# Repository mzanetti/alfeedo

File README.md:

# Alfeedo

A fully featured, smart home integrated cat feeder. 

This repository contains the firmware for the 3D printed cat feeder Alfeedo.

## Features

* Controls a TMC2209 stepper motor to dispense food (including jam detection and recovery)
* Supports operation and setup using a 128x32 display and Buttons
* Built-in web interface
* REST API

| Main view | Timer settings | Logs | Settings |
| :--- | :--- | :--- | :--- |
|  |  |  |  |

## How to build

3D print model files along with a bill of materials are available on Makerworld. 

[Makerworld - Alfeedo](https://makerworld.com/en/models/2506745-alfeedo-smart-cat-feeder)

Follow print and assembly instructions provided with the model files.

Electronics wiring can be simplified by ordering the Alfeedo PCB using the provided Gerber files in [pcb/](https://github.com/mzanetti/alfeedo/tree/main/pcb).

-Flash the device using the [web flasher](https://mzanetti.github.io/alfeedo/main/flasher/).

-Connect with the Alfeedo-WIFI-AP

-Navigate to alfeedo.local and set network credentials.

Note that the provided firmware assumes wiring to look like on the Alfeedo PCB. If instead you prefer using a different setup, you'll have to build the firmware yourself and adjust the pins in hwsettings.h.

## Building

This project is based on [platformio](https://platformio.org/).

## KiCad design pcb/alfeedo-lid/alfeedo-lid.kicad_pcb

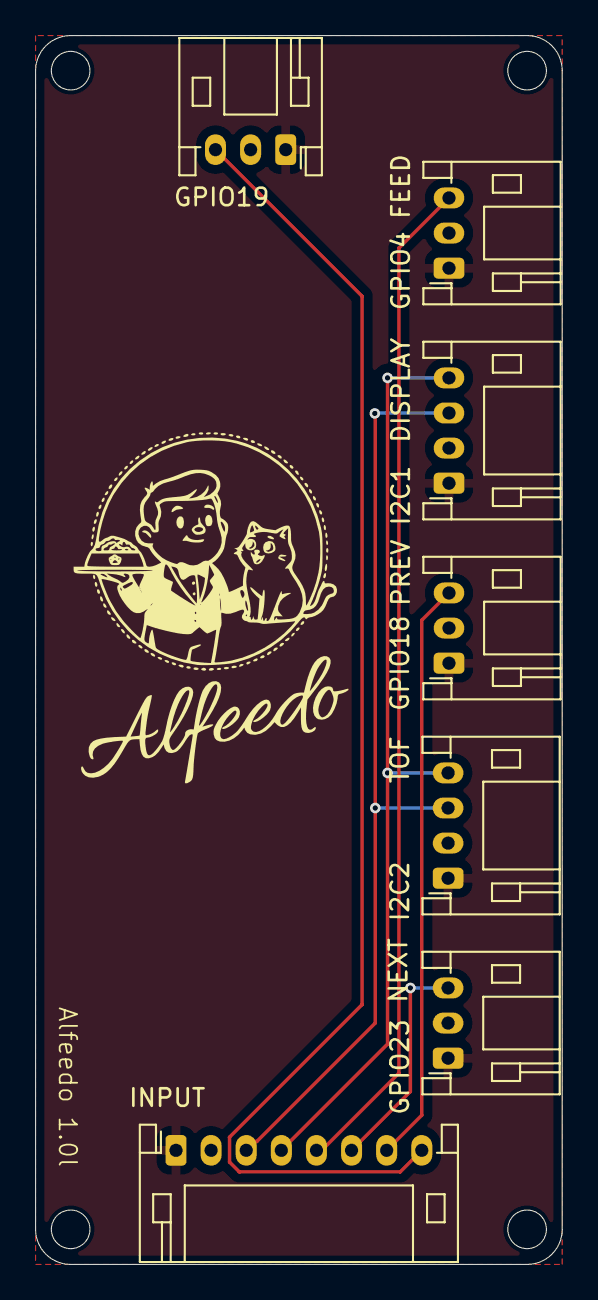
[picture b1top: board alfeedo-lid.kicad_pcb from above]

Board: 2 copper layers, 30.0 x 70.0 mm, 11 parts (0 on the bottom side), 8 nets.

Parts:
GPIO4: FEED; JST_PH_S3B-PH-K_1x03_P2.00mm_Horizontal
GPIO18: PREV; JST_PH_S3B-PH-K_1x03_P2.00mm_Horizontal
GPIO19: RESERVED; JST_PH_S3B-PH-K_1x03_P2.00mm_Horizontal
GPIO23: NEXT; JST_PH_S3B-PH-K_1x03_P2.00mm_Horizontal
H1, H2, H3, H4: MountingHole; MountingHole_2.2mm_M2
I2C1: DISPLAY; JST_PH_S4B-PH-K_1x04_P2.00mm_Horizontal
I2C2: TOF; JST_PH_S4B-PH-K_1x04_P2.00mm_Horizontal
J1: INPUT; JST_PH_S8B-PH-K_1x08_P2.00mm_Horizontal

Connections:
/GND: GPIO4.2, GPIO18.2, GPIO19.2, GPIO23.2, I2C1.2, I2C2.2, J1.2
/GPIO_FEED: GPIO4.3, J1.5
/GPIO_NEXT: GPIO23.3, J1.6
/GPIO_PREV: GPIO18.3, J1.7
/GPIO_RESERVED: GPIO19.3, J1.8
/PWR: GPIO4.1, GPIO18.1, GPIO19.1, GPIO23.1, I2C1.1, I2C2.1, J1.1
/SCL: I2C1.4, I2C2.4, J1.4
/SDA: I2C1.3, I2C2.3, J1.3

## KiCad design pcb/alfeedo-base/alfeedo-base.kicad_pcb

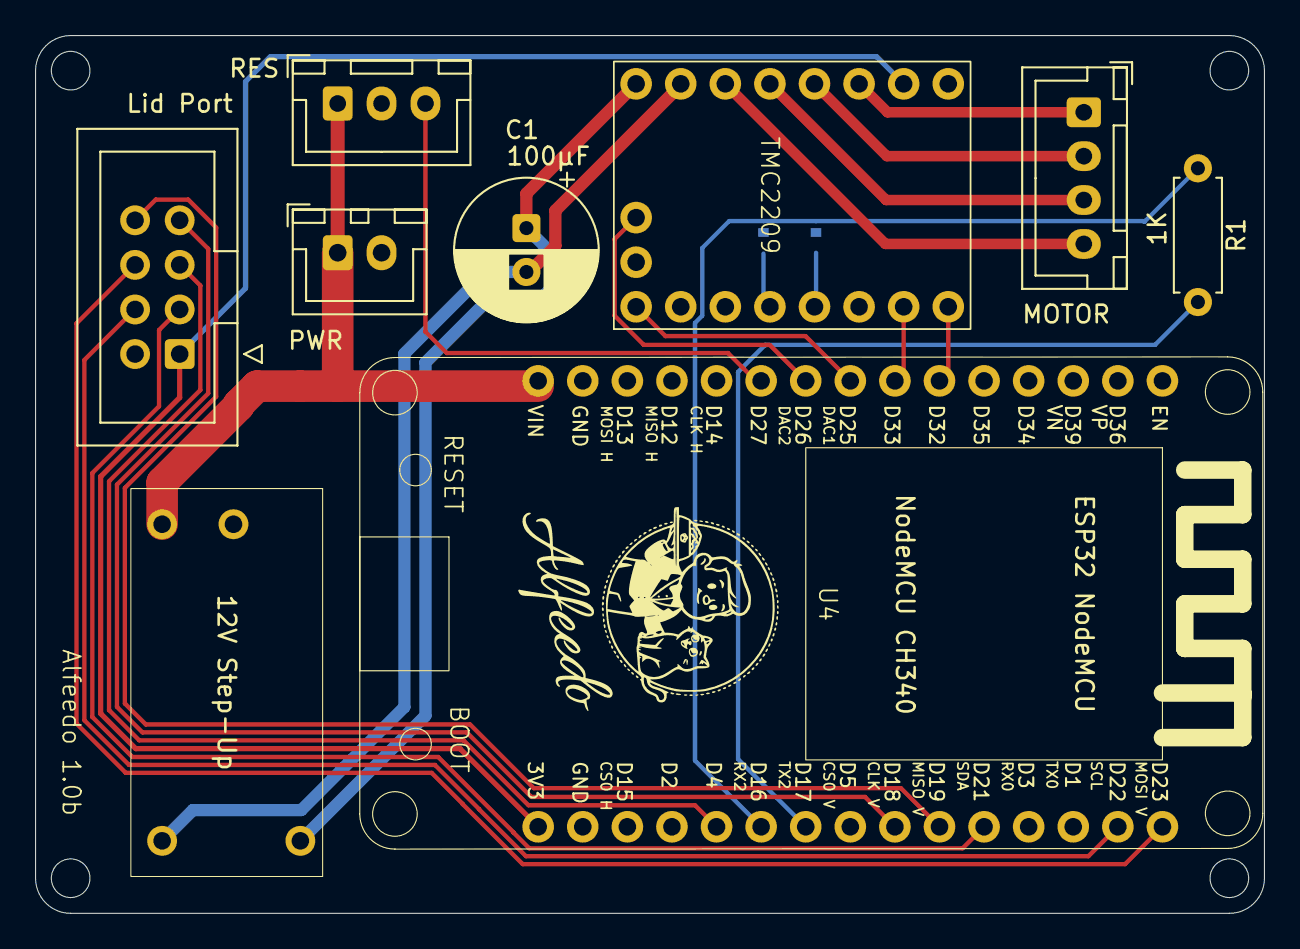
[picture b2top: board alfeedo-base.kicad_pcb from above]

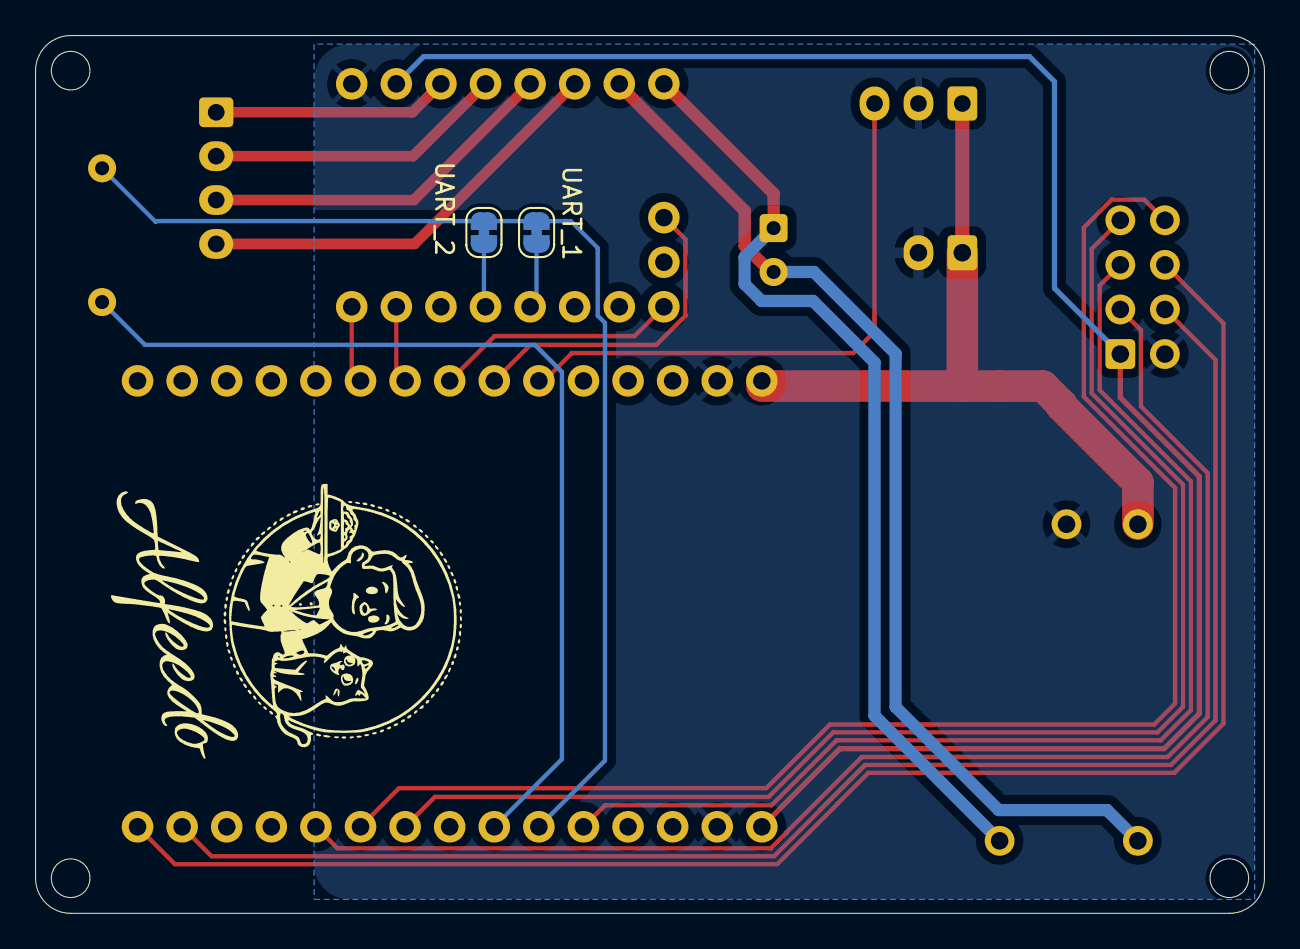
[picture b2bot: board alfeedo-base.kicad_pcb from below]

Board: 2 copper layers, 70.0 x 50.0 mm, 15 parts (2 on the bottom side), 24 nets.

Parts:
C1: 100µF; CP_Radial_D8.0mm_P2.50mm
H1, H2, H3, H4: MountingHole; MountingHole_2.2mm_M2
J1: RES; JST_XH_B3B-XH-A_1x03_P2.50mm_Vertical
J4: PWR; JST_XH_B2B-XH-A_1x02_P2.50mm_Vertical
J6: MOTOR; JST_XH_B4B-XH-A_1x04_P2.50mm_Vertical
JP1: UART_2; SolderJumper-2_P1.3mm_Bridged_RoundedPad1.0x1.5mm
JP2: UART_1; SolderJumper-2_P1.3mm_Bridged_RoundedPad1.0x1.5mm
R1: 1K; R_Axial_DIN0207_L6.3mm_D2.5mm_P7.62mm_Horizontal
TMC2209: TMC2209
U1: 12V Step-Up; 12V Step-up
U2: Lid Port; IDC-Header_2x04_P2.54mm_Vertical
U4: ESP32 NodeMCU; NodeMCU CH340

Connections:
/3.3V: TMC2209.15 (VDD), U2.1 (3.3V), U4.30 (3.3V)
/GND: J1.2, J4.2, TMC2209.16 (GND), U1.1 (-IN), U2.2 (GND), U4.14 (GND), U4.29 (GND)
/GND_M: C1.2, TMC2209.10 (GND_M), U1.3 (-OUT)
/GPIO_DIAG: TMC2209.18 (DIAG), U4.9 (D26)
/GPIO_DIR: TMC2209.8 (DIR), U4.6 (D32)
/GPIO_EN: TMC2209.1 (EN), U4.8 (D25)
/GPIO_FEED: U2.5 (BTN_FEED), U4.26 (D4)
/GPIO_NEXT: U2.6 (BTN_NEXT), U4.16 (D23/MOSI)
/GPIO_PREV: U2.7 (BTN_PREV), U4.22 (D18/CLK)
/GPIO_RES: U2.8 (RES), U4.21 (D19/MISO)
/GPIO_STEP: TMC2209.7 (STEP), U4.7 (D33)
/Motor_A1: J6.3, TMC2209.12 (A1)
/Motor_A2: J6.4, TMC2209.11 (A2)
/Motor_B1: J6.2, TMC2209.13 (B1)
/Motor_B2: J6.1, TMC2209.14 (B2)
/SCL: U2.4 (SCL), U4.17 (D22/SCL)
/SDA: U2.3 (SDA), U4.20 (D21/SDA)
/UART_RX: JP1.1 (A), JP2.1 (A), R1.2, U4.25 (D16/RX2)
/UART_TX: R1.1, U4.24 (D17/TX2)
/VIN: J1.1, J4.1, U1.2 (+IN), U4.15 (VIN)
/V_M: C1.1, TMC2209.9 (VM), U1.4 (+OUT)
unnamed: J1.3, U4.10 (D27)
unnamed: JP1.2 (B), TMC2209.5 (PDN_UART_TX)
unnamed: JP2.2 (B), TMC2209.4 (PDN_UART_RX)

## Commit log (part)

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2026-03-02 Initial import
2026-03-02 Add github action
    Add github action to build with platformio
2026-03-02 Build with newer toolchain
2026-03-02 archive artifacts
2026-03-02 deploy: 7b175032e379fcab0c805f331938c22b007cf090
2026-03-03 Add github pages publish
2026-03-03 deploy: 23218cf0d6253eb7ced624008aa3cf3002dfaa0b
2026-03-05 Add readme
2026-03-05 deploy: 239e08357cc172759e9d33b5e1d7c040f844ebf4
2026-03-05 Fix flasher link in readme
2026-03-05 deploy: 9a7da3ad369b4ba0fda9e09d33b76d69a89e938f
2026-03-10 Add the Alfeedo PCB project
2026-03-10 deploy: 6268aa2f706c28d2feadaae456896bbed0065af3
2026-03-10 deploy: e5fa76ff595c3aa507c2746b428ea25bdec9ba74
2026-03-10 add makerworld link
2026-03-10 deploy: 5c7397c2a3277d9e49b764121e0a5ad6c058b78d
2026-03-28 deploy: c870660d0060e21fbc9c7678781c29f088263605
2026-03-28 Pin newer pioarduino toolkit
2026-03-28 deploy: 01db9a645c21d1296fc64b022b68c0d7e8ac0ff0
2026-03-28 deploy: b87227a54986d808307cd28f81c79c7a5be8c503
2026-06-10 Add gear ratio setting
